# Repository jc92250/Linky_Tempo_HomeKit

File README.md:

# Linky_Tempo_HomeKit

** work in progress **  
Status actuel: démontrateur technique de la partie HomeKit sur platine d'essai

## Présentation

Ceci est la "V2" du projet Linky_Tempo.  
L'objectif est de pouvoir accéder au status du délestage ainsi qu'à la possibilité d'annuler ce délestage depuis Internet.

L'approche suivie sera de:
- remplacer l'Arduino par un ESP32
- installer HomeSpan sur l'ESP32 pour qu'il soit vu comme un device HomeKit
- le configurer comme un "Thermostat"

Pourquoi "Thermostat" ?  
Car cela semble être le device dont les fonctionnalités sont les plus proches de celles qu'on veut obtenir.  
Voici ses différents modes de fonctionnement (CurrentHeatingCoolingState) et leur usage prévu:
- IDLE: utilisé, délestage possible en fonction des infos du Linky
- HEATING: délestage annulé, chauffage actif
- COOLING: pas utilisé

Concernant la commande (TargetHeatingCoolingState) on a:
- OFF: pas utilisé
- HEAT: annulation du délestage, activer le chauffage (sauf si surconsommation)
- COOL: pas utilisé
- AUTO: mode automatique (délestage HPJR, HPJW et surconsommation)

Le circuit a également un bouton poussoir permettant de basculer entre le mode automatique et le mode annulation du délestage

Note: "Heater-Cooler" aurait peut-être pu être utilisé à la place de "Thermostat". Mais cette possibilité n'a pas été étudiée.

## Configuration

Factory reset:  
Faire un appui long (> 10 secondes) sur le bouton reset. Au bout de 3 secondes, la led interne va clignoter rapidement, continuer l'appui sur le bouton jusqu'à l'extinction de la led

Pour configurer le device, faire comme suit:
- Alimenter le device  
- Faire un appui long sur le bouton reset pour entrer dans le mode configuration
- relacher lorsque la led interne clignote rapidement
- Faire deux appuis courts sur le bouton pour sélectionner l'option de paramétrage du WiFi
- Faire un appui semi-long (3 secondes) pour entrer dans ce mode
- Depuis un ordinateur ou un smartphone, se connecter au Wifi du device (nom du réseau: JCDELESTAGE, mot de passe: 123456789)
- dans la page web qui s'affiche, entrer les paramètres de votre Wifi puis entrer un code HomeKit

Ceci fait, il est maintenant possible d'associer le device à Maison

## Les LEDs

LED rouge: toujours allumée, indique que l'ESP32 est alimenté  
LED bleue:  
- allumée fixe: le device est en fonctionnement et pairé dans Maison  
- allumée et clignotante (2 flashs brefs toutes les 3 secondes): le device n'est pas pairé dans Maison

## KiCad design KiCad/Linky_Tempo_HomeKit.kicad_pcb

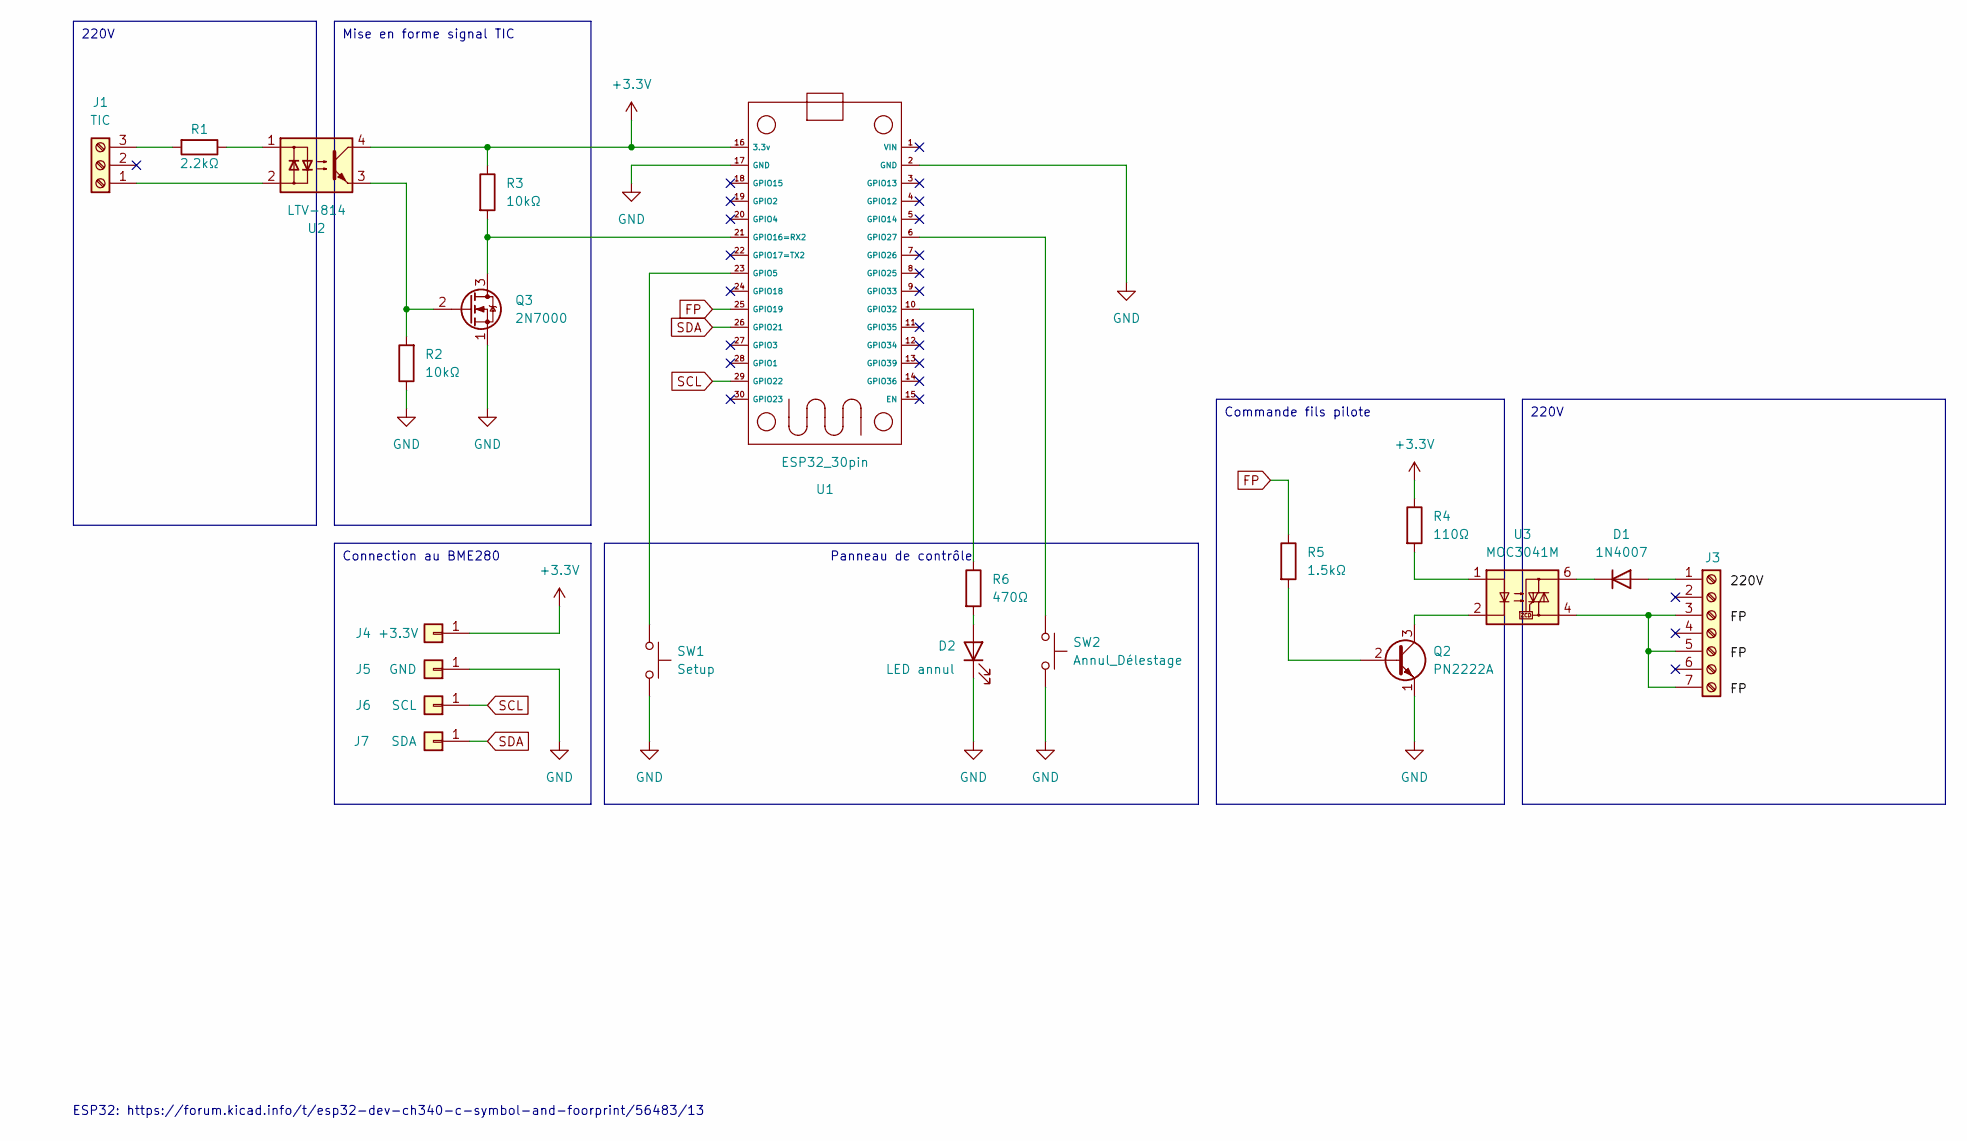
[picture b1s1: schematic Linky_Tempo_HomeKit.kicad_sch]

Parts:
D1: 1N4007; D_DO-15_P15.24mm_Horizontal
D2: LED annul; LED_D3.0mm
J1: TIC; PinSocket_1x03_P2.54mm_Vertical
J3: Main(1) + Fil pilote (3,5,7); PinSocket_1x07_P2.54mm_Vertical
J4: +3.3V; PinHeader_1x01_P2.54mm_Vertical
J5: GND; PinHeader_1x01_P2.54mm_Vertical
J6: SCL; PinHeader_1x01_P2.54mm_Vertical
J7: SDA; PinHeader_1x01_P2.54mm_Vertical
Q2: PN2222A; TO-92_Inline_Wide
Q3: 2N7000; TO-92_Inline
R1: 2.2kΩ; R_Axial_DIN0207_L6.3mm_D2.5mm_P2.54mm_Vertical
R2: 10kΩ; R_Axial_DIN0207_L6.3mm_D2.5mm_P2.54mm_Vertical
R3: 10kΩ; R_Axial_DIN0309_L9.0mm_D3.2mm_P12.70mm_Horizontal
R4: 110Ω; R_Axial_DIN0207_L6.3mm_D2.5mm_P5.08mm_Vertical
R5: 1.5kΩ; R_Axial_DIN0309_L9.0mm_D3.2mm_P20.32mm_Horizontal
R6: 470Ω; R_Axial_DIN0204_L3.6mm_D1.6mm_P7.62mm_Horizontal
SW1: Setup; SW_PUSH_5.08mm_H5mm
SW2: Annul_Délestage; SW_PUSH_5.08mm_H5mm
U1: ESP32_30pin
U2: LTV-814; DIP-4_W7.62mm
U3: MOC3041M; DIP-6_W7.62mm

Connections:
+3.3V: J4.1, R3.1, R4.1, U1.16 (3.3v), U2.4
FP: R5.1, U1.25 (GPIO19)
GND: D2.1 (K), J5.1, Q2.1 (E), Q3.1 (S), R2.1, SW1.2, SW2.2, U1.2 (GND), U1.17 (GND)
unnamed: D1.2 (A), J3.1
unnamed: D1.1 (K), U3.6
unnamed: D2.2 (A), R6.2
unnamed: J1.1, U2.2
unnamed: J1.3, R1.2
unnamed: J3.3, J3.5, J3.7, U3.4
unnamed: Q2.2 (B), R5.2
unnamed: Q2.3 (C), U3.2
unnamed: Q3.3 (D), R3.2, U1.21 (GPIO16=RX2)
unnamed: Q3.2 (G), R2.2, U2.3
unnamed: R1.1, U2.1
unnamed: R4.2, U3.1
unnamed: SW1.1, U1.23 (GPIO5)
unnamed: SW2.1, U1.6 (GPIO27)
unnamed: R6.1, U1.10 (GPIO32)
SCL: J6.1, U1.29 (GPIO22)
SDA: J7.1, U1.26 (GPIO21)

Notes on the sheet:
Connection au BME280
Commande fils pilote
220V
Panneau de contrôle
Mise en forme signal TIC
ESP32: https://forum.kicad.info/t/esp32-dev-ch340-c-symbol-and-foorprint/56483/13

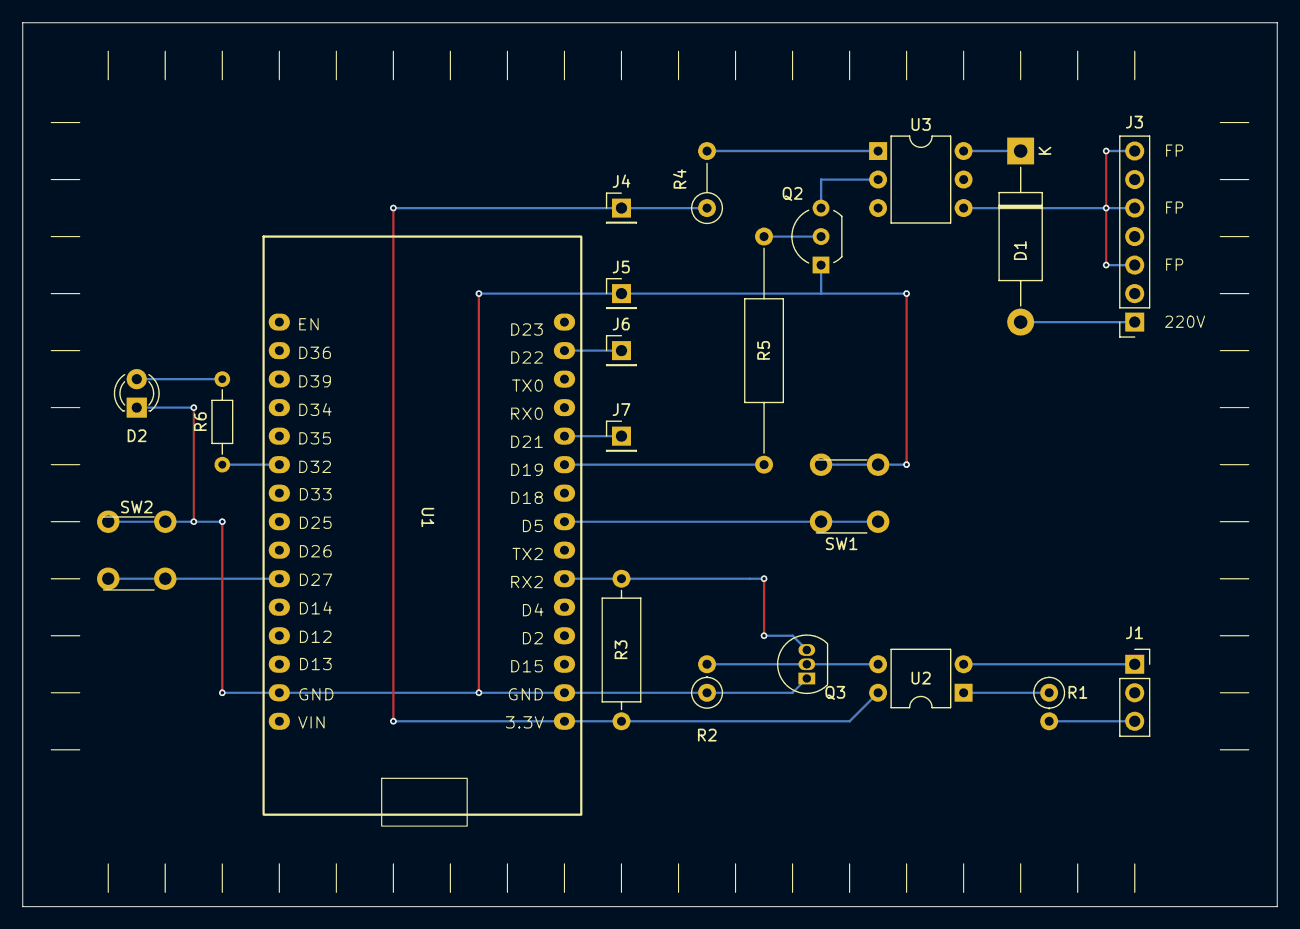
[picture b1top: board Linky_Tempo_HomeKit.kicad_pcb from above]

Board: 2 copper layers, 111.8 x 78.7 mm, 21 parts (0 on the bottom side), 20 nets.

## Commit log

2024-12-24 first version
2024-12-28 corrections diverses
2024-12-28 hotspot activé automatiquement après reset
